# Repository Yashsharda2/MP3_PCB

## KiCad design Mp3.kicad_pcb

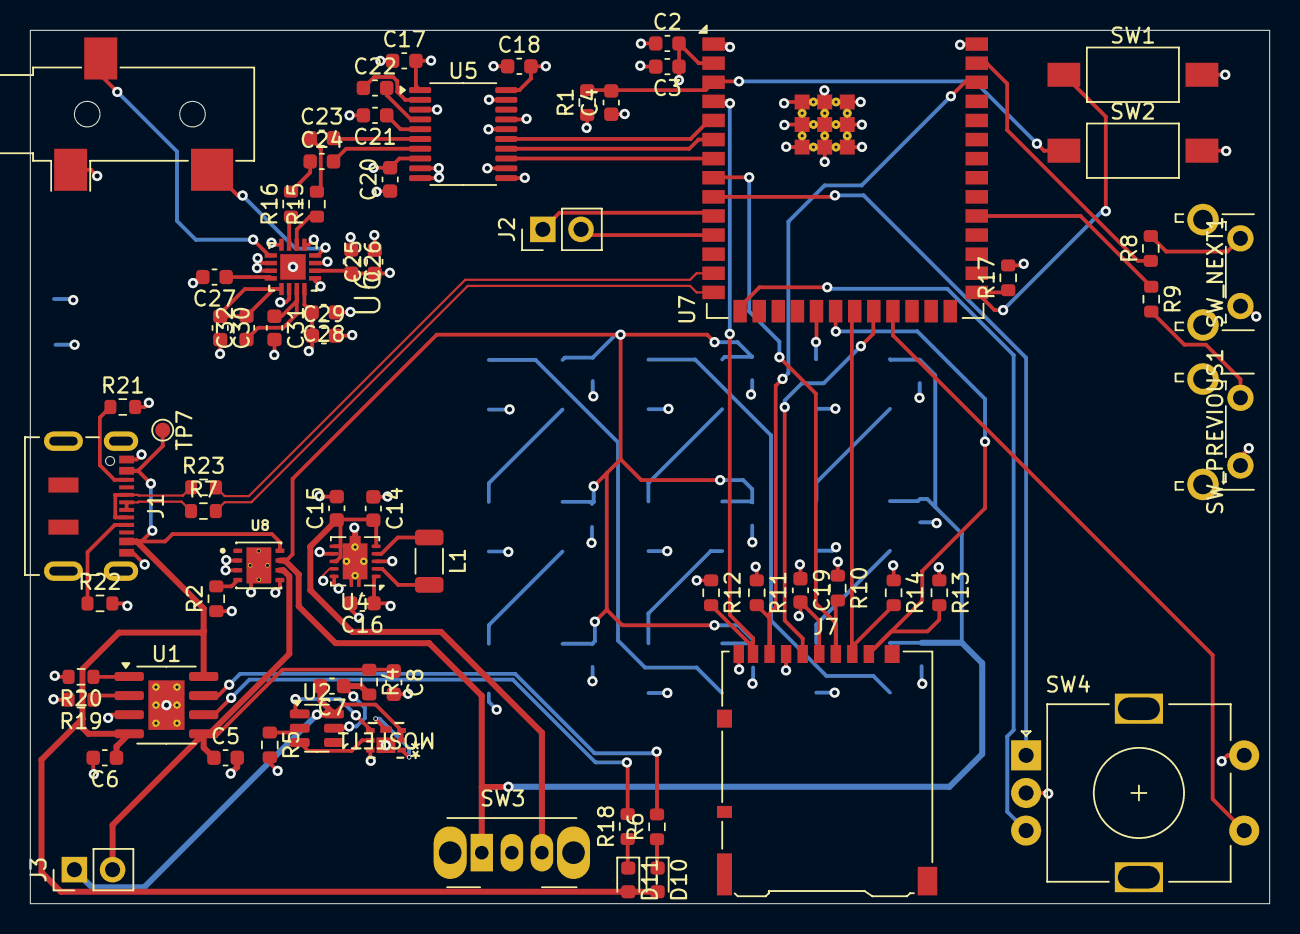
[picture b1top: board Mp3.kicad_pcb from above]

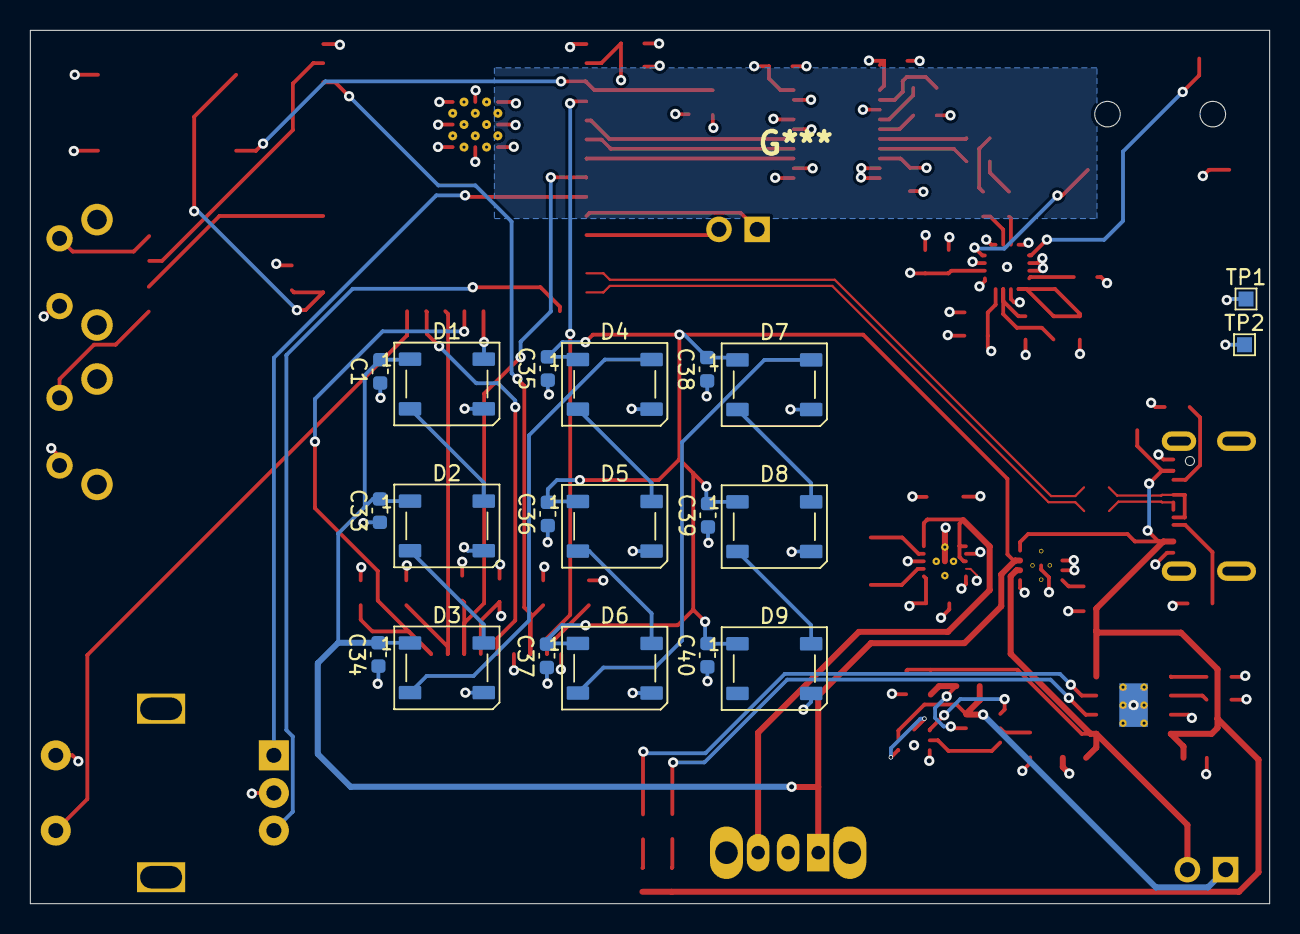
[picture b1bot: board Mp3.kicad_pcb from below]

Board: 4 copper layers, 82.4 x 58.1 mm, 91 parts (20 on the bottom side), 68 nets.

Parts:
C1, C17, C18, C19, C20, C26, C28, C33, C34, C35, C36, C37, C38, C39, C40: 100nF; C_0603_1608Metric
C2, C7: 100n; C_0603_1608Metric
C3, C5, C6, C8: 10u; C_0603_1608Metric
C4: 0.1u; C_0603_1608Metric
C14, C15: 10µF; C_0603_1608Metric
C16: 22µF; C_0603_1608Metric
C21, C22: 2.2µF; C_0603_1608Metric
C23, C24, C25, C27, C29, C30, C31, C32: 1u; C_0603_1608Metric
D1, D2, D3, D4, D5, D6, D7, D8, D9: WS2812B; LED_WS2812B_PLCC4_5.0x5.0mm_P3.2mm
D10, D11: LED; LED_0603_1608Metric
J1: USB_C_Receptacle_USB2.0_16P; USB_C_Receptacle_JAE_DX07S016JA1R1500
J2, J3: Conn_01x02; PinHeader_1x02_P2.54mm_Vertical
J7: Micro_SD_Card; microSD_HC_Hirose_DM3AT-SF-PEJM5
J8: AudioJack3; Jack_3.5mm_CUI_SJ-3523-SMT_Horizontal
L1: 2.2uH; L_1206_3216Metric
MOSFET1: DMTH6016LFDFWQ-7R; U-DFN2020-6_TYPE_F_DIO
R1, R10, R11, R12, R13, R14, R17: 10k; R_0603_1608Metric
R2: 402; R_0603_1608Metric
R4, R15, R16: 100; R_0603_1608Metric
R5, R6, R8, R9, R18, R19: 1k; R_0603_1608Metric
R7, R23: 22; R_0603_1608Metric
R20: 0; R_0603_1608Metric
R21, R22: 5.1k; R_0603_1608Metric
SW1: boot; SW_SPST_FSMSM
SW2: reset; SW_SPST_FSMSM
SW3: SW_Wuerth_450301014042; SW_Slide_SPDT_Angled_CK_OS102011MA1Q
SW4: RotaryEncoder_Switch; RotaryEncoder_Alps_EC11E-Switch_Vertical_H20mm
SW_NEXT1: SW_Push; SW_Tactile_SPST_Angled_PTS645Vx83-2LFS
SW_PREVIOUS1: SW_Push; SW_Tactile_SPST_Angled_PTS645Vx83-2LFS
TP1, TP2: TestPoint; TestPoint_Pad_1.0x1.0mm
TP7: GND; TestPoint_Pad_D1.0mm
U1: TP4056-42-ESOP8; SOIC-8-1EP_3.9x4.9mm_P1.27mm_EP2.41x3.3mm_ThermalVias
U2: DW01A; SOT-23-6
U4: TPS63001; Texas_DRC0010J_ThermalVias
U5: PCM5102A; TSSOP-20_4.4x6.5mm_P0.65mm
U6: TPA6132A2RTE; QFN50P300X300X80-16N
U7: ESP32-S3-WROOM-2
U8: TPS2113ADRBR; SON65P300X300X100-9N

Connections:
+3V3: C2.2, C3.1, C16.1, C17.2, C18.2, C19.2, C20.2, C25.1, C26.2, C28.2, C29.1, J7.4 (VDD), R1.1, R10.1, R11.1, R12.1, R13.1, R14.1, R17.2, TP1.1, U4.1 (VOUT), U4.10 (FB), U5.1 (CPVDD), U5.8 (AVDD), U5.17 (XSMT), U5.20 (DVDD), U6.12 (HPVDD), U6.13 (EN), U6.14 (VDD), U7.2 (3V3)
EN: C4.2, R1.2, SW2.1, U7.3 (EN)
GND: C1.1, C2.1, C3.2, C4.1, C5.2, C6.2, C8.2, C14.1, C15.2, C16.2, C17.1, C18.1, C19.1, C20.1, C21.2, C25.2, C26.1, C27.2, C28.1, C29.2, C30.2, C31.2, C33.1, C34.1, C35.1, C36.1, C37.1, C38.1, C39.1, C40.1, D1.3 (VSS), D2.3 (VSS), D3.3 (VSS), D4.3 (VSS), D5.3 (VSS), D6.3 (VSS), D7.3 (VSS), D8.3 (VSS), D9.3 (VSS), J1.A1 (GND), J1.A12 (GND), J1.B1 (GND), J1.B12 (GND), J1.S1 (SHIELD), J7.6 (VSS), J7.9 (SHIELD), J8.S, MOSFET1.6, MOSFET1.7, R2.1, R5.2, R19.2, R20.2, R21.2, R22.2, SW1.2, SW2.2, SW4.C, SW4.S2, SW_NEXT1.2, SW_PREVIOUS1.2, TP2.1, U1.3 (GND), U1.9 (EPAD), U4.3 (PGND), U4.7 (PS/SYNC), U4.9 (GND), U4.11 (PGND), U5.3 (CPGND), U5.9 (AGND), U5.10 (DEMP), U5.11 (FLT), U5.12 (SCK), U5.16 (FMT), U5.19 (DGND), U6.1 (INL-), U6.4 (INR-), U6.6 (G0), U6.7 (G1), U6.10 (PGND), U6.15 (SGND), U6.17 (EP), U7.1 (GND), U7.40 (GND), U7.41 (GND), U8.2 (~EN), U8.3 (VSNS), U8.5 (GND), U8.9 (GND)
GP3: SW4.B, U7.15 (IO3)
GP16: SW4.A, U7.9 (IO16)
GP21: SW4.S1, U7.23 (IO21)
GPIO0: R17.1, SW1.1, U7.27 (IO0)
GPIO1: R8.1, U7.39 (IO1)
GPIO17: J2.1, U7.10 (IO17)
GPIO18: J2.2, U7.11 (IO18)
GPIO38: R9.1, U7.31 (IO38)
I2S_BCK: U5.13 (BCK), U7.7 (IO7)
I2S_DATA: U5.14 (DIN), U7.6 (IO6)
I2S_WS: U5.15 (LRCK), U7.5 (IO5)
INL+: R15.1, U6.2 (INL+)
INR+: R16.1, U6.3 (INR+)
LED_DIN: D1.4 (DIN), U7.19 (IO11)
MUX_OUT: C1.2, C33.2, C34.2, C35.2, C36.2, C37.2, C38.2, C39.2, C40.2, D1.1 (VDD), D2.1 (VDD), D3.1 (VDD), D4.1 (VDD), D5.1 (VDD), D6.1 (VDD), D7.1 (VDD), D8.1 (VDD), D9.1 (VDD), SW3.1 (B), U8.7 (OUT)
unnamed: C23.1, R15.2
unnamed: C24.1, R16.2
unnamed: D1.2 (DOUT), D2.4 (DIN)
unnamed: D2.2 (DOUT), D3.4 (DIN)
unnamed: D3.2 (DOUT), D4.4 (DIN)
unnamed: D4.2 (DOUT), D5.4 (DIN)
unnamed: D5.2 (DOUT), D6.4 (DIN)
unnamed: D6.2 (DOUT), D7.4 (DIN)
unnamed: D7.2 (DOUT), D8.4 (DIN)
unnamed: D8.2 (DOUT), D9.4 (DIN)
unnamed: D10.1 (K), R6.1
unnamed: D11.1 (K), R18.1
unnamed: J1.A5 (CC1), R21.1
unnamed: J1.B5 (CC2), R22.1
unnamed: MOSFET1.1, MOSFET1.8
unnamed: R8.2, SW_NEXT1.1
unnamed: R9.2, SW_PREVIOUS1.1
unnamed: R19.1, U1.2 (PROG)
unnamed: R20.1, U1.1 (TEMP)
unnamed: R6.2, U1.7 (~CHRG)
unnamed: R18.2, U1.6 (~STDBY)
unnamed: R5.1, U2.2 (CS)
unnamed: C7.1, R4.2, U2.5 (VCC)
unnamed: L1.1, U4.4 (L1)
unnamed: L1.2, U4.2 (L2)
unnamed: C22.2, U5.4 (CAPM)
unnamed: C22.1, U5.2 (CAPP)
unnamed: C23.2, U5.6 (OUTL)
unnamed: C24.2, U5.7 (OUTR)
unnamed: C21.1, U5.5 (VNEG)
unnamed: C30.1, C32.2, U6.9 (CPN)
unnamed: C31.1, C32.1, U6.11 (CPP)
unnamed: C27.1, U6.8 (HPVSS)
unnamed: R2.2, U8.4 (ILIM)
OC: MOSFET1.5, U2.3 (OC)
OD: MOSFET1.4, U2.1 (OD)
OUTL: J8.T, U6.16 (OUTL)
OUTR: J8.R, U6.5 (OUTR)
SD_CLK: J7.5 (CLK), U7.22 (IO14)
SD_CMD: J7.3 (CMD), R10.2, U7.8 (IO15)
SD_D0: J7.7 (DAT0), R11.2, U7.38 (IO2)
SD_D1: J7.8 (DAT1), R12.2, U7.4 (IO4)
SD_D2: J7.1 (DAT2), R13.2, U7.20 (IO12)
SD_D3: J7.2 (DAT3/CD), R14.2, U7.21 (IO13)
SL_OUT: C14.2, C15.1, SW3.3 (A), U4.5 (VIN), U4.6 (EN), U4.8 (VINA)
USB_D+: J1.A6 (D+), J1.B6 (D+), R7.1, R7.2, U7.14 (USB_D+/IO20)
USB_D-: J1.A7 (D-), J1.B7 (D-), R23.1, R23.2, U7.13 (USB_D-/IO19)
VBUS: C6.1, D10.2 (A), D11.2 (A), J1.A4 (VBUS), J1.A9 (VBUS), J1.B4 (VBUS), J1.B9 (VBUS), TP7.1, U1.4 (V_{CC}), U1.8 (CE), U8.8 (IN1)
VS_BAT: C7.2, J3.1, MOSFET1.2, MOSFET1.3, U2.6 (GND)
V_BAT: C5.1, C8.1, J3.2, R4.1, U1.5 (BAT), U8.6 (IN2)
